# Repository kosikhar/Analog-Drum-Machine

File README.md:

# Analog-Drum-Machine
Capstone 2019 Analog Drum Machine project.

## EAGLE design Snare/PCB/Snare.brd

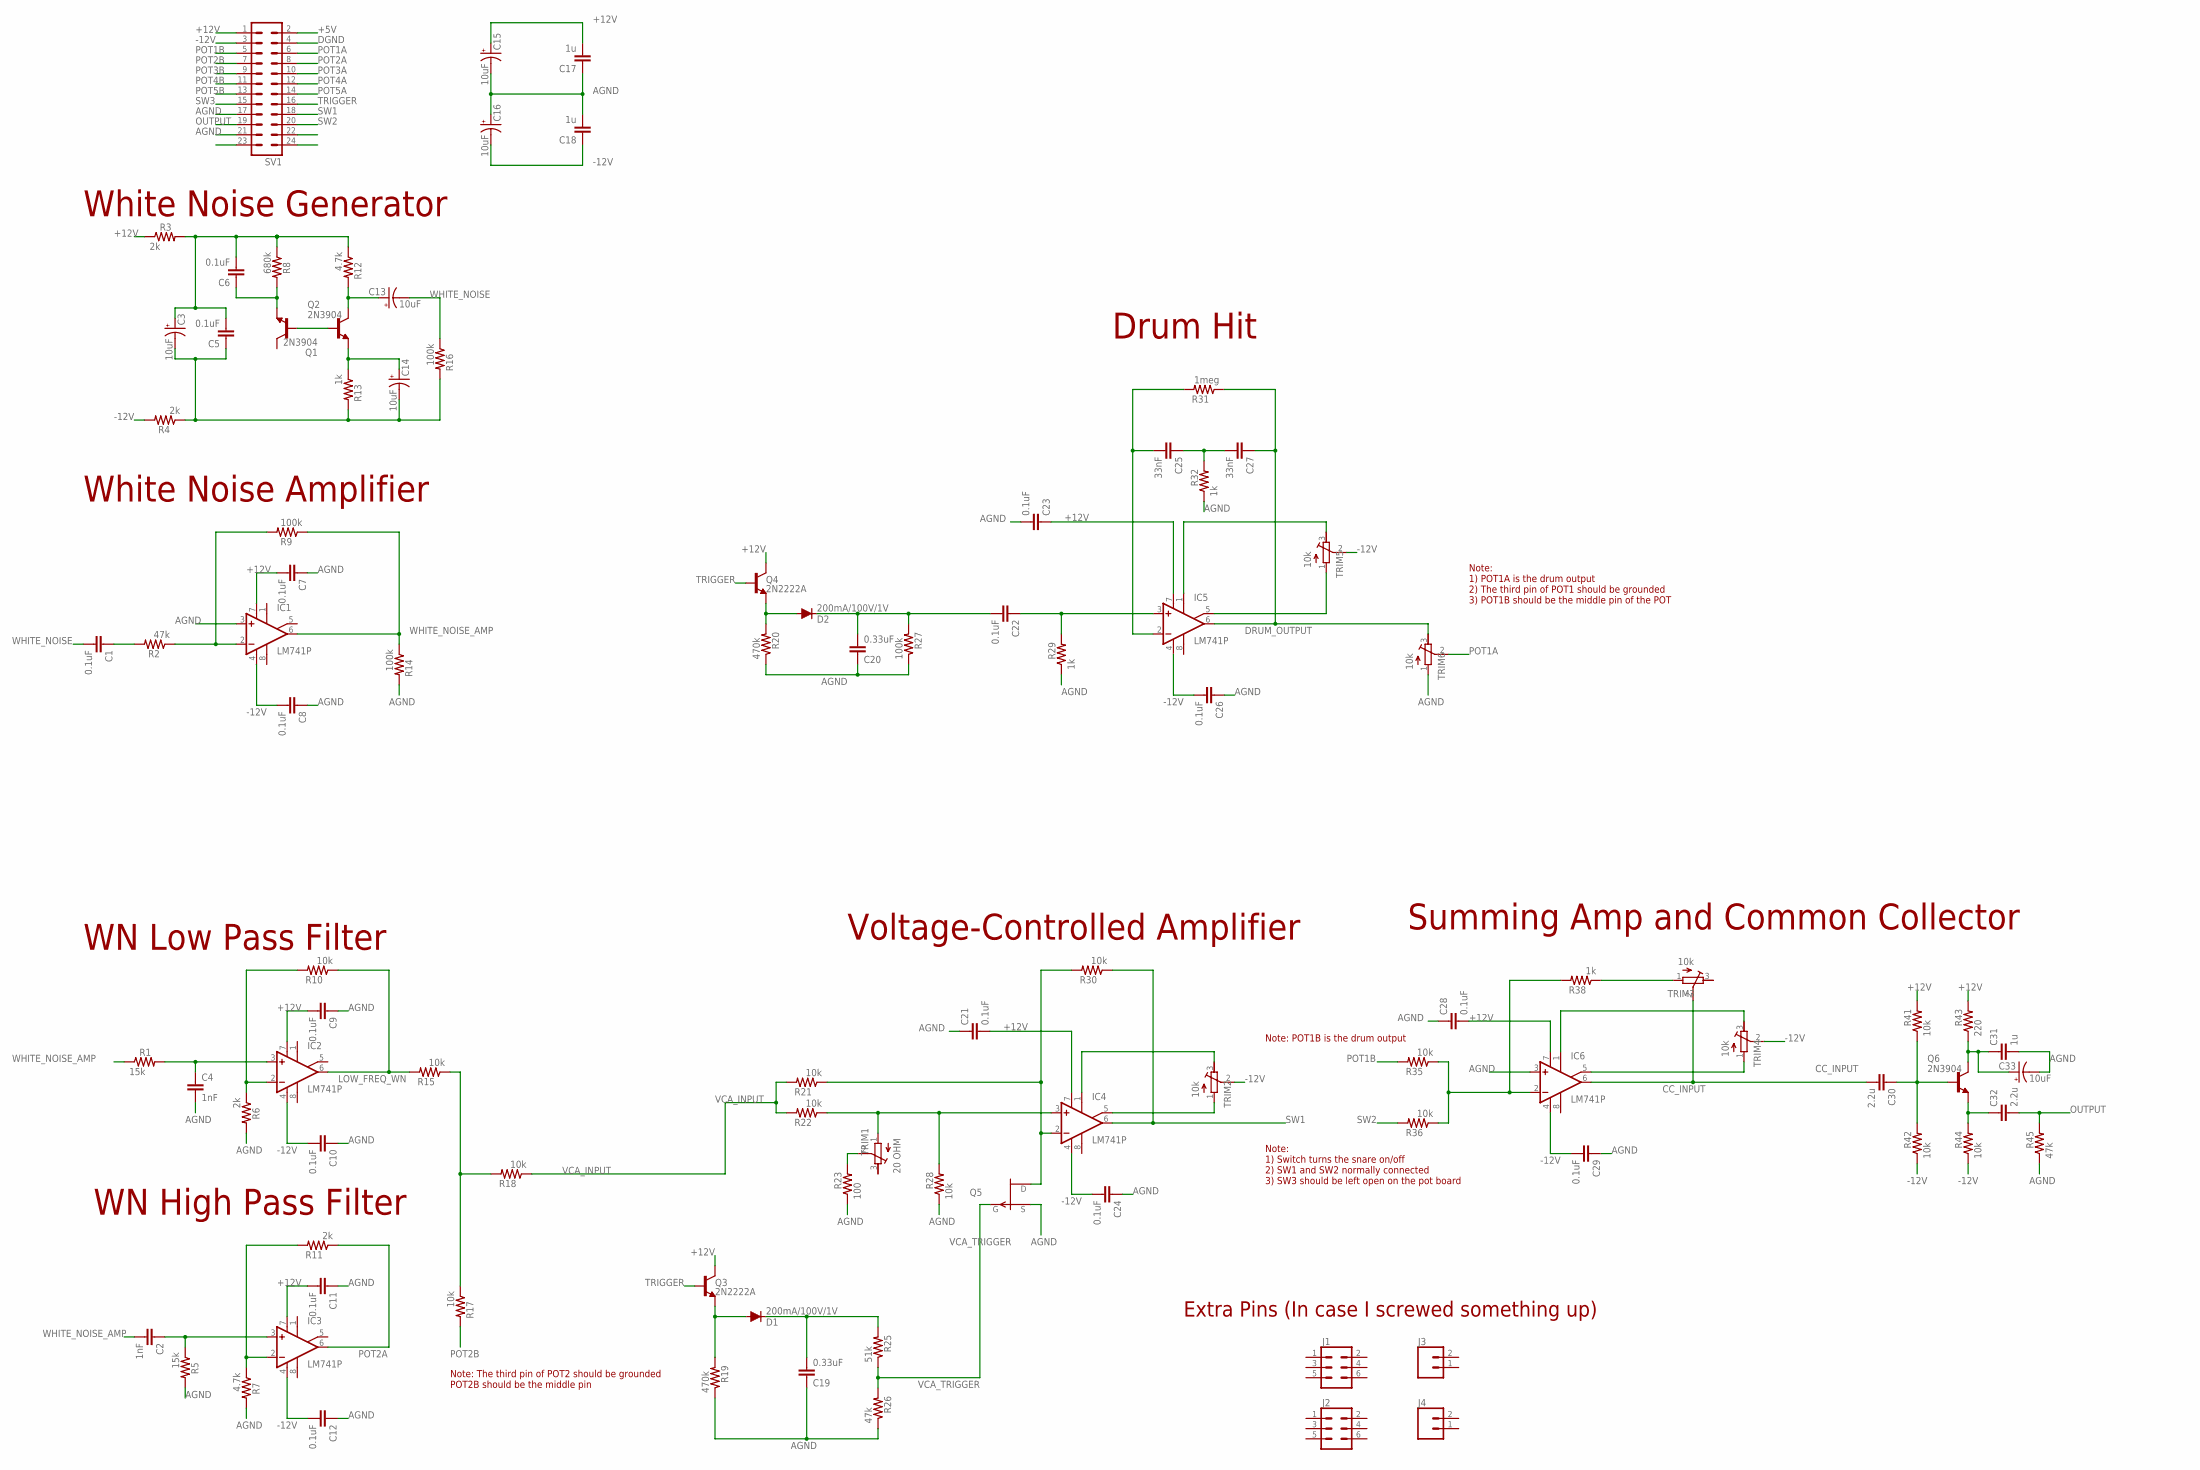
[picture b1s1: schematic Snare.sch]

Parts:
C1, C5, C6, C7, C8, C9, C10, C11, C12, C21, C22, C23, C24, C26, C28, C29: 0.1uF; C050-024X044
C2, C4: 1nF; C050-024X044
C3, C13, C14, C15, C16, C33: 10uF; E2,5-6
C17, C18, C31: 1u; C050-024X044
C19, C20: 0.33uF; C050-024X044
C25, C27: 33nF; C050-024X044
C30, C32: 2.2u; C050-024X044
D1, D2: 200mA/100V/1V; DIODE-1N4148
IC1, IC2, IC3, IC4, IC5, IC6: LM741P; DIL08
J1, J2: CONN_03X2NO_SILK; 2X3-NS
J3, J4: CONN_021X02_NO_SILK; 1X02_NO_SILK
Q1, Q2, Q6: 2N3904; TO92
Q3, Q4: 2N2222A; TO-92
Q5: J176; TO-92
R1, R5: 15k; 0207/10
R2, R26, R45: 47k; 0207/10
R3, R4, R6, R11: 2k; 0207/10
R7, R12: 4.7k; 0207/10
R8: 680k; 0207/10
R9, R14, R16, R27: 100k; 0207/10
R10, R15, R17, R18, R21, R22, R28, R30, R35, R36, R41, R42, R44: 10k; 0207/10
R13, R29, R32, R38: 1k; 0207/10
R19, R20: 470k; 0207/10
R23: 100; 0207/10
R25: 51k; 0207/10
R31: 1meg; 0207/10
R43: 220; 0207/10
SV1: MA12-2
TRIM1: 20 OHM; RTRIM64W
TRIM2, TRIM3, TRIM4, TRIM5, TRIM6: 10k; RTRIM64W

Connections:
+5V: SV1.2
+12V: C7.2, C9.2, C11.2, C15.+, C17.2, C21.2, C23.1, C28.2, IC1.7 (V+), IC2.7 (V+), IC3.7 (V+), IC4.7 (V+), IC5.7 (V+), IC6.7 (V+), Q3.1 (C), Q4.1 (C), R3.1, R41.2, R43.2, SV1.1
-12V: C8.2, C10.2, C12.2, C16.-, C18.1, C24.2, C26.2, C29.2, IC1.4 (V-), IC2.4 (V-), IC3.4 (V-), IC4.4 (V-), IC5.4 (V-), IC6.4 (V-), R4.2, R42.1, R44.1, SV1.3, TRIM2.2 (S), TRIM4.2 (S), TRIM5.2 (S)
AGND: C4.2, C7.1, C8.1, C9.1, C10.1, C11.1, C12.1, C15.-, C16.+, C17.1, C18.2, C19.1, C20.1, C21.1, C23.2, C24.1, C26.1, C28.1, C29.1, C31.2, C33.-, IC1.3 (+IN), IC6.3 (+IN), Q5.3 (S), R5.2, R6.2, R7.2, R14.2, R19.1, R20.1, R23.1, R26.1, R27.1, R28.1, R29.1, R32.1, R45.1, SV1.17, SV1.21, TRIM6.1 (A)
CC_INPUT: C30.2, IC6.6 (OUT), TRIM3.2 (S)
DGND: SV1.4
DRUM_OUTPUT: C27.1, IC5.6 (OUT), R31.1, TRIM6.3 (E)
unnamed: R15.1, R17.1, R18.2
unnamed: IC6.2 (-IN), R35.1, R36.1, R38.2
unnamed: R38.1, TRIM3.1 (A)
unnamed: IC6.5 (ON2), TRIM4.1 (A)
unnamed: C14.+, Q2.3 (E), R13.1
unnamed: C3.+, C5.2, C6.2, R3.2, R8.1, R12.1
unnamed: IC6.1 (ON1), TRIM4.3 (E)
unnamed: C25.1, C27.2, R32.2
unnamed: Q1.2 (B), Q2.2 (B)
unnamed: C6.1, Q1.3 (E), R8.2
unnamed: C3.-, C5.1, C14.-, R4.1, R13.2, R16.2
unnamed: IC1.2 (-IN), R2.1, R9.2
unnamed: IC3.2 (-IN), R7.1, R11.2
unnamed: C1.1, R2.2
unnamed: C13.+, Q2.1 (C), R12.2
unnamed: C2.1, IC3.3 (+IN), R5.1
unnamed: IC2.2 (-IN), R6.1, R10.2
unnamed: C4.1, IC2.3 (+IN), R1.2
unnamed: C20.2, C22.2, D2.C, R27.2
unnamed: C30.1, Q6.2 (B), R41.1, R42.2
unnamed: C32.1, Q6.3 (E), R44.2
unnamed: C31.1, C33.+, Q6.1 (C), R43.1
unnamed: D2.A, Q4.3 (E), R20.2
unnamed: C22.1, IC5.3 (+IN), R29.2
unnamed: R23.2, TRIM1.2 (S)
unnamed: C25.2, IC5.2 (-IN), R31.2
unnamed: IC5.1 (ON1), TRIM5.3 (E)
unnamed: IC5.5 (ON2), TRIM5.1 (A)
unnamed: IC4.3 (+IN), R22.1, R28.2, TRIM1.1 (A)
unnamed: IC4.2 (-IN), Q5.1 (D), R21.1, R30.2
unnamed: IC4.1 (ON1), TRIM2.3 (E)
unnamed: C19.2, D1.C, R25.2
unnamed: IC4.5 (ON2), TRIM2.1 (A)
unnamed: D1.A, Q3.3 (E), R19.2
OUTPUT: C32.2, R45.2, SV1.19
POT1A: SV1.6, TRIM6.2 (S)
POT1B: R35.2, SV1.5
POT2B: R17.2, SV1.7
POT3A: SV1.10
POT3B: SV1.9
POT4A: SV1.12
POT4B: SV1.11
POT5A: SV1.14
POT5B: SV1.13
SW1: IC4.6 (OUT), R30.1, SV1.18
SW2: R36.2, SV1.20
SW3: SV1.15
TRIGGER: Q3.2 (B), Q4.2 (B), SV1.16
VCA_INPUT: R18.1, R21.2, R22.2
VCA_TRIGGER: Q5.2 (G), R25.1, R26.2
WHITE_NOISE: C1.2, C13.-, R16.1

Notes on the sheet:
Note: The third pin of POT2 should be grounded POT2B should be the middle pin
Note: 1) POT1A is the drum output 2) The third pin of POT1 should be grounded 3) POT1B should be the middle pin of the POT
Note: POT1B is the drum output
Note: 1) Switch turns the snare on/off 2) SW1 and SW2 normally connected 3) SW3 should be left open on the pot board
White Noise Generator
White Noise Amplifier
WN Low Pass Filter
WN High Pass Filter
Drum Hit
Voltage-Controlled Amplifier
Summing Amp and Common Collector
Extra Pins (In case I screwed something up)

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
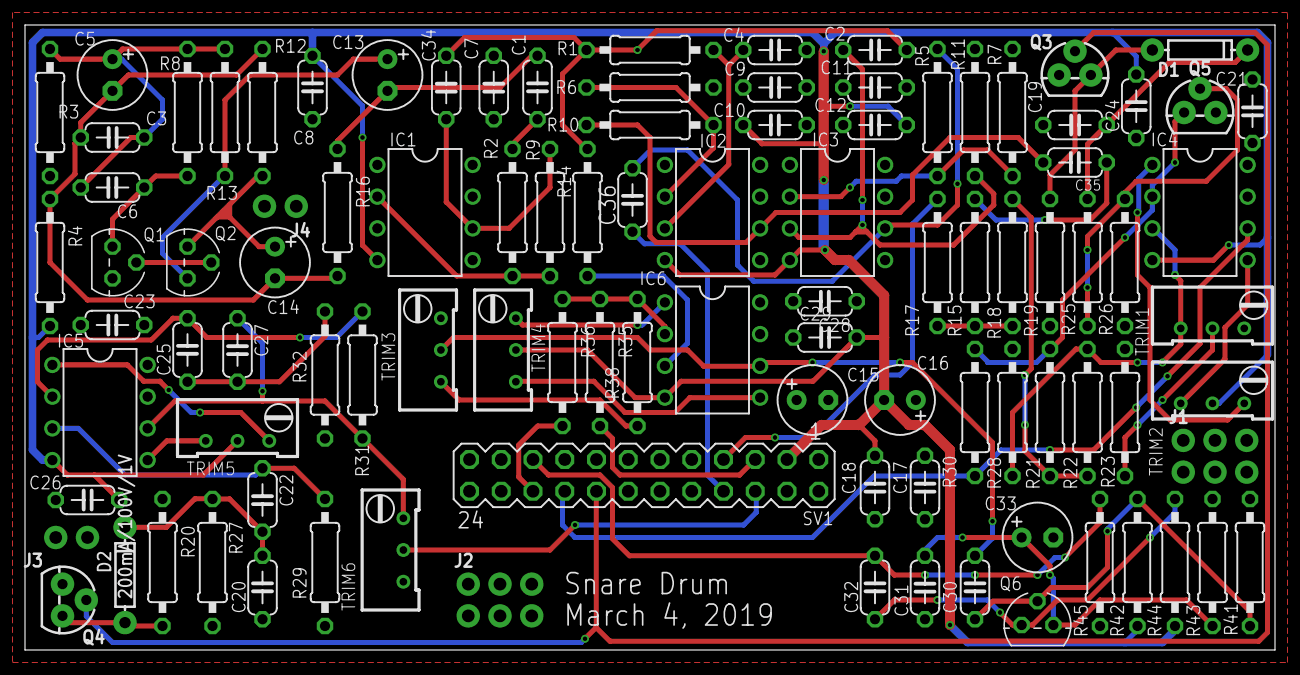
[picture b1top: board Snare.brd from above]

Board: 2 copper layers, 100.0 x 50.0 mm, 100 parts (0 on the bottom side), 55 nets.

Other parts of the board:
C34, C35, C36: 0.1uF; C050-024X044

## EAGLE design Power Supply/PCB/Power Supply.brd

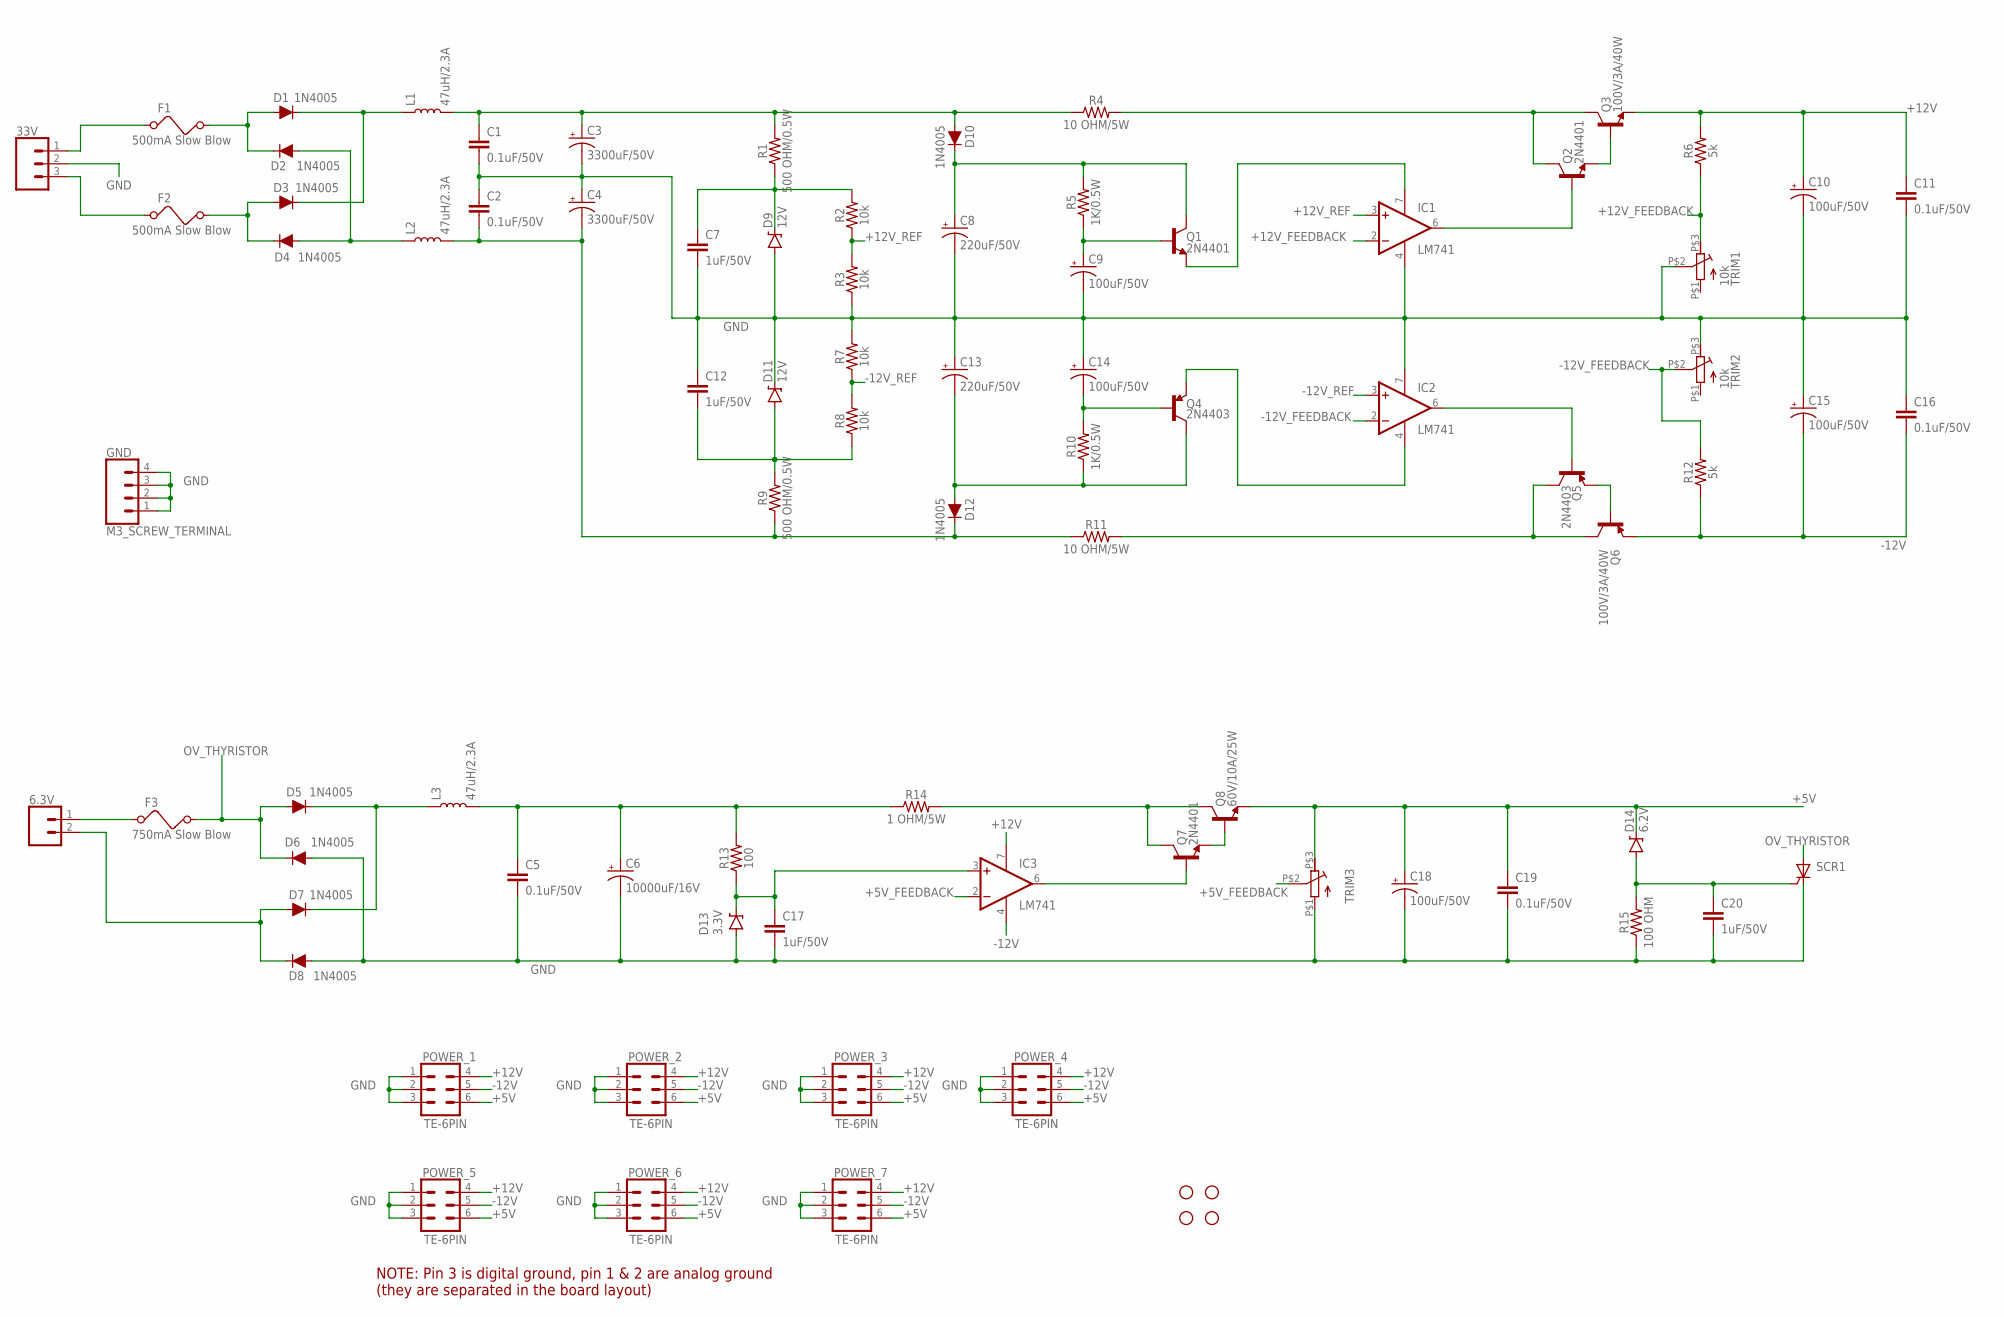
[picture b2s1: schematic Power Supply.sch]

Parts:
6.3V: TE-2PIN; 2_PIN_CONNECT
33V: TE-3PIN; 3_PIN_TE
C1, C2, C5, C11, C16, C19: 0.1uF/50V; CERAMIC_CAPACITOR
C3, C4: 3300uF/50V; POLARIZED_CAP_3300UF
C6: 10000uF/16V; POLARIZED_CAP_3300UF
C7, C12, C17, C20: 1uF/50V; CERAMIC_CAPACITOR
C8, C13: 220uF/50V; 220UF_CAP
C9, C10, C14, C15, C18: 100uF/50V; 100UF_CAP
D1, D2, D3, D4, D5, D6, D7, D8, D10, D12: 1N4005; DIODE-1N4001
D9, D11: 12V; 1W_ZENER
D13: 3.3V; 1W_ZENER
D14: 6.2V; 1W_ZENER
F1, F2: 500mA Slow Blow; FUSEHOLDER
F3: 750mA Slow Blow; FUSEHOLDER
GND: M3_SCREW_TERMINAL
H1, H2, H3, H4: STAND-OFF
IC1, IC2, IC3: LM741; DIL08
L1, L2, L3: 47uH/2.3A; 47UH_2.3A_COIL
POWER_1, POWER_2, POWER_3, POWER_4, POWER_5, POWER_6, POWER_7: TE-6PIN; TE_6_PIN
Q1, Q2, Q7: 2N4401; TO-92
Q3, Q6: 100V/3A/40W; TO-220_LARGE_HEATSINK
Q4, Q5: 2N4403; TO-92
Q8: 60V/10A/25W; TO-220_SMALL_HEATSINK
R1, R9: 500 OHM/0.5W; 0.5W_RES
R2, R3, R7, R8: 10k; 0.25W_RES
R4, R11: 10 OHM/5W; 5W_RES
R5, R10: 1K/0.5W; 0.5W_RES
R6, R12: 5k; 0.25W_RES
R13: 100; 0.25W_RES
R14: 1 OHM/5W; 5W_RES
R15: 100 OHM; 0.25W_RES
SCR1: THYRISTOR_4A; TO220V
TRIM1, TRIM2: 10k; 10K_TRIM
TRIM3: 10K_TRIMMER; 10K_TRIM

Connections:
+5V: C18.P1+ (+), C19.P$1 (1), D14.P$2CATHODE (C), POWER_1.6, POWER_2.6, POWER_3.6, POWER_4.6, POWER_5.6, POWER_6.6, POWER_7.6, Q8.P$3 (E), TRIM3.P$3 (E)
+5V_FEEDBACK: IC3.2 (-IN), TRIM3.P$2 (S)
+12V: C10.P1+ (+), C11.P$1 (1), IC3.7 (V+), POWER_1.4 (2), POWER_2.4 (2), POWER_3.4 (2), POWER_4.4 (2), POWER_5.4 (2), POWER_6.4 (2), POWER_7.4 (2), Q3.P$3 (E), R6.P$2 (2)
+12V_FEEDBACK: IC1.2 (-IN), R6.P$1 (1), TRIM1.P$3 (E)
+12V_REF: IC1.3 (+IN), R2.P$1 (1), R3.P$2 (2)
-12V: C15.P2- (-), C16.P$2 (2), IC3.4 (V-), POWER_1.5 (4), POWER_2.5 (4), POWER_3.5 (4), POWER_4.5 (4), POWER_5.5 (4), POWER_6.5 (4), POWER_7.5 (4), Q6.P$3 (E), R12.P$1 (1)
-12V_FEEDBACK: IC2.2 (-IN), R12.P$2 (2), TRIM2.P$2 (S)
-12V_REF: IC2.3 (+IN), R7.P$1 (1), R8.P$2 (2)
GND: 33V.2, C1.P$2 (2), C2.P$1 (1), C3.P2- (-), C4.P1+ (+), C5.P$2 (2), C6.P2- (-), C7.P$2 (2), C8.P2- (-), C9.P2- (-), C10.P2- (-), C11.P$2 (2), C12.P$1 (1), C13.P1+ (+), C14.P1+ (+), C15.P1+ (+), C16.P$1 (1), C17.P$2 (2), C18.P2- (-), C19.P$2 (2), C20.P$2 (2), D6.A, D8.A, D9.P$1ANODE (A), D11.P$2CATHODE (C), D13.P$1ANODE (A), GND.1, GND.2, GND.3, GND.4, IC1.4 (V-), IC2.7 (V+), POWER_1.1, POWER_1.2 (3), POWER_1.3 (5), POWER_2.1, POWER_2.2 (3), POWER_2.3 (5), POWER_3.1, POWER_3.2 (3), POWER_3.3 (5), POWER_4.1, POWER_4.2 (3), POWER_4.3 (5), POWER_5.1, POWER_5.2 (3), POWER_5.3 (5), POWER_6.1, POWER_6.2 (3), POWER_6.3 (5), POWER_7.1, POWER_7.2 (3), POWER_7.3 (5), R3.P$1 (1), R7.P$2 (2), R15.P$1 (1), SCR1.1 (C), TRIM1.P$2 (S), TRIM2.P$3 (E), TRIM3.P$1 (A)
unnamed: D1.C, D3.C, L1.P$1 (1)
unnamed: D1.A, D2.C, F1.P$2 (2)
unnamed: D3.A, D4.C, F2.P$2 (2)
unnamed: D2.A, D4.A, L2.P$1 (1)
unnamed: 33V.1 (3), F1.P$1 (1)
unnamed: 33V.3 (1), F2.P$1 (1)
unnamed: C1.P$1 (1), C3.P1+ (+), D10.A, L1.P$2 (2), R1.P$2 (2), R4.P$1 (1)
unnamed: C8.P1+ (+), D10.C, Q1.3 (C), R5.P$2 (2)
unnamed: C2.P$2 (2), C4.P2- (-), D12.C, L2.P$2 (2), R9.P$1 (1), R11.P$1 (1)
unnamed: C9.P1+ (+), Q1.2 (B), R5.P$1 (1)
unnamed: IC1.7 (V+), Q1.1 (E)
unnamed: Q2.3 (C), Q3.P$2 (C), R4.P$2 (2)
unnamed: Q2.1 (E), Q3.P$1 (B)
unnamed: IC1.6 (OUT), Q2.2 (B)
unnamed: C7.P$1 (1), D9.P$2CATHODE (C), R1.P$1 (1), R2.P$2 (2)
unnamed: C13.P2- (-), D12.A, Q4.3 (C), R10.P$1 (1)
unnamed: C17.P$1 (1), D13.P$2CATHODE (C), IC3.3 (+IN), R13.P$1 (1)
unnamed: C12.P$2 (2), D11.P$1ANODE (A), R8.P$1 (1), R9.P$2 (2)
unnamed: 6.3V.1 (2), F3.P$1 (1)
unnamed: C14.P2- (-), Q4.2 (B), R10.P$2 (2)
unnamed: IC2.4 (V-), Q4.1 (E)
unnamed: Q5.3 (C), Q6.P$2 (C), R11.P$2 (2)
unnamed: Q5.1 (E), Q6.P$1 (B)
unnamed: IC2.6 (OUT), Q5.2 (B)
unnamed: Q7.3 (C), Q8.P$2 (C), R14.P$2 (2)
unnamed: 6.3V.2 (1), D7.A, D8.C
unnamed: IC3.6 (OUT), Q7.2 (B)
unnamed: D5.C, D7.C, L3.P$1 (1)
unnamed: C5.P$1 (1), C6.P1+ (+), L3.P$2 (2), R13.P$2 (2), R14.P$1 (1)
unnamed: Q7.1 (E), Q8.P$1 (B)
unnamed: C20.P$1 (1), D14.P$1ANODE (A), R15.P$2 (2), SCR1.3 (G)
OV_THYRISTOR: D5.A, D6.C, F3.P$2 (2), SCR1.2 (A)

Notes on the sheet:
NOTE: Pin 3 is digital ground, pin 1 & 2 are analog ground (they are separated in the board layout)

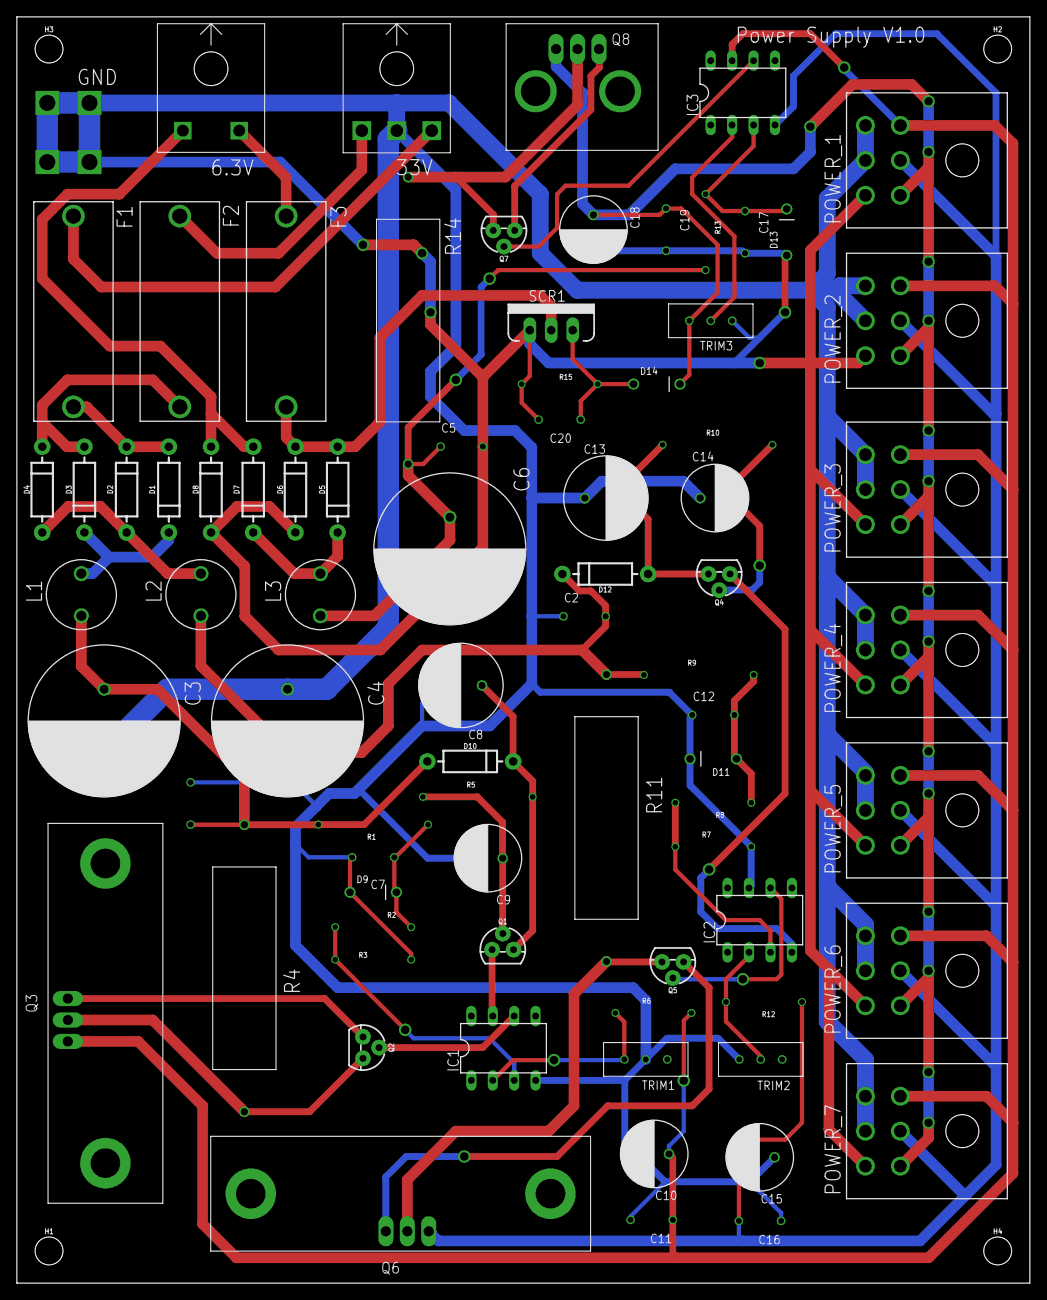
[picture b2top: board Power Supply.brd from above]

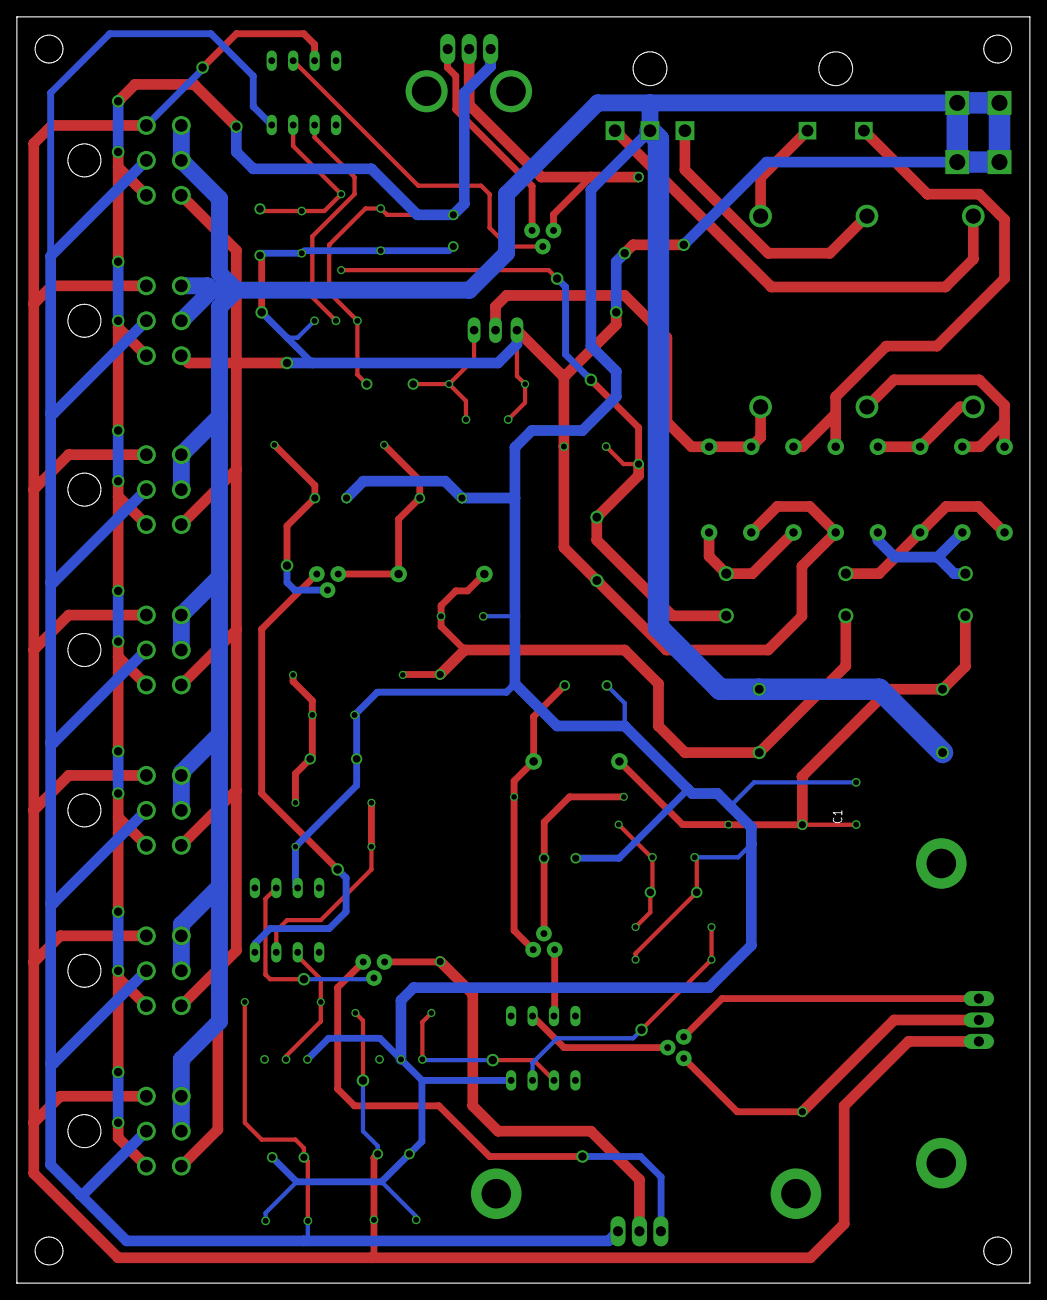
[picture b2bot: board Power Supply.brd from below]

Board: 2 copper layers, 120.0 x 150.0 mm, 84 parts (2 on the bottom side), 41 nets.

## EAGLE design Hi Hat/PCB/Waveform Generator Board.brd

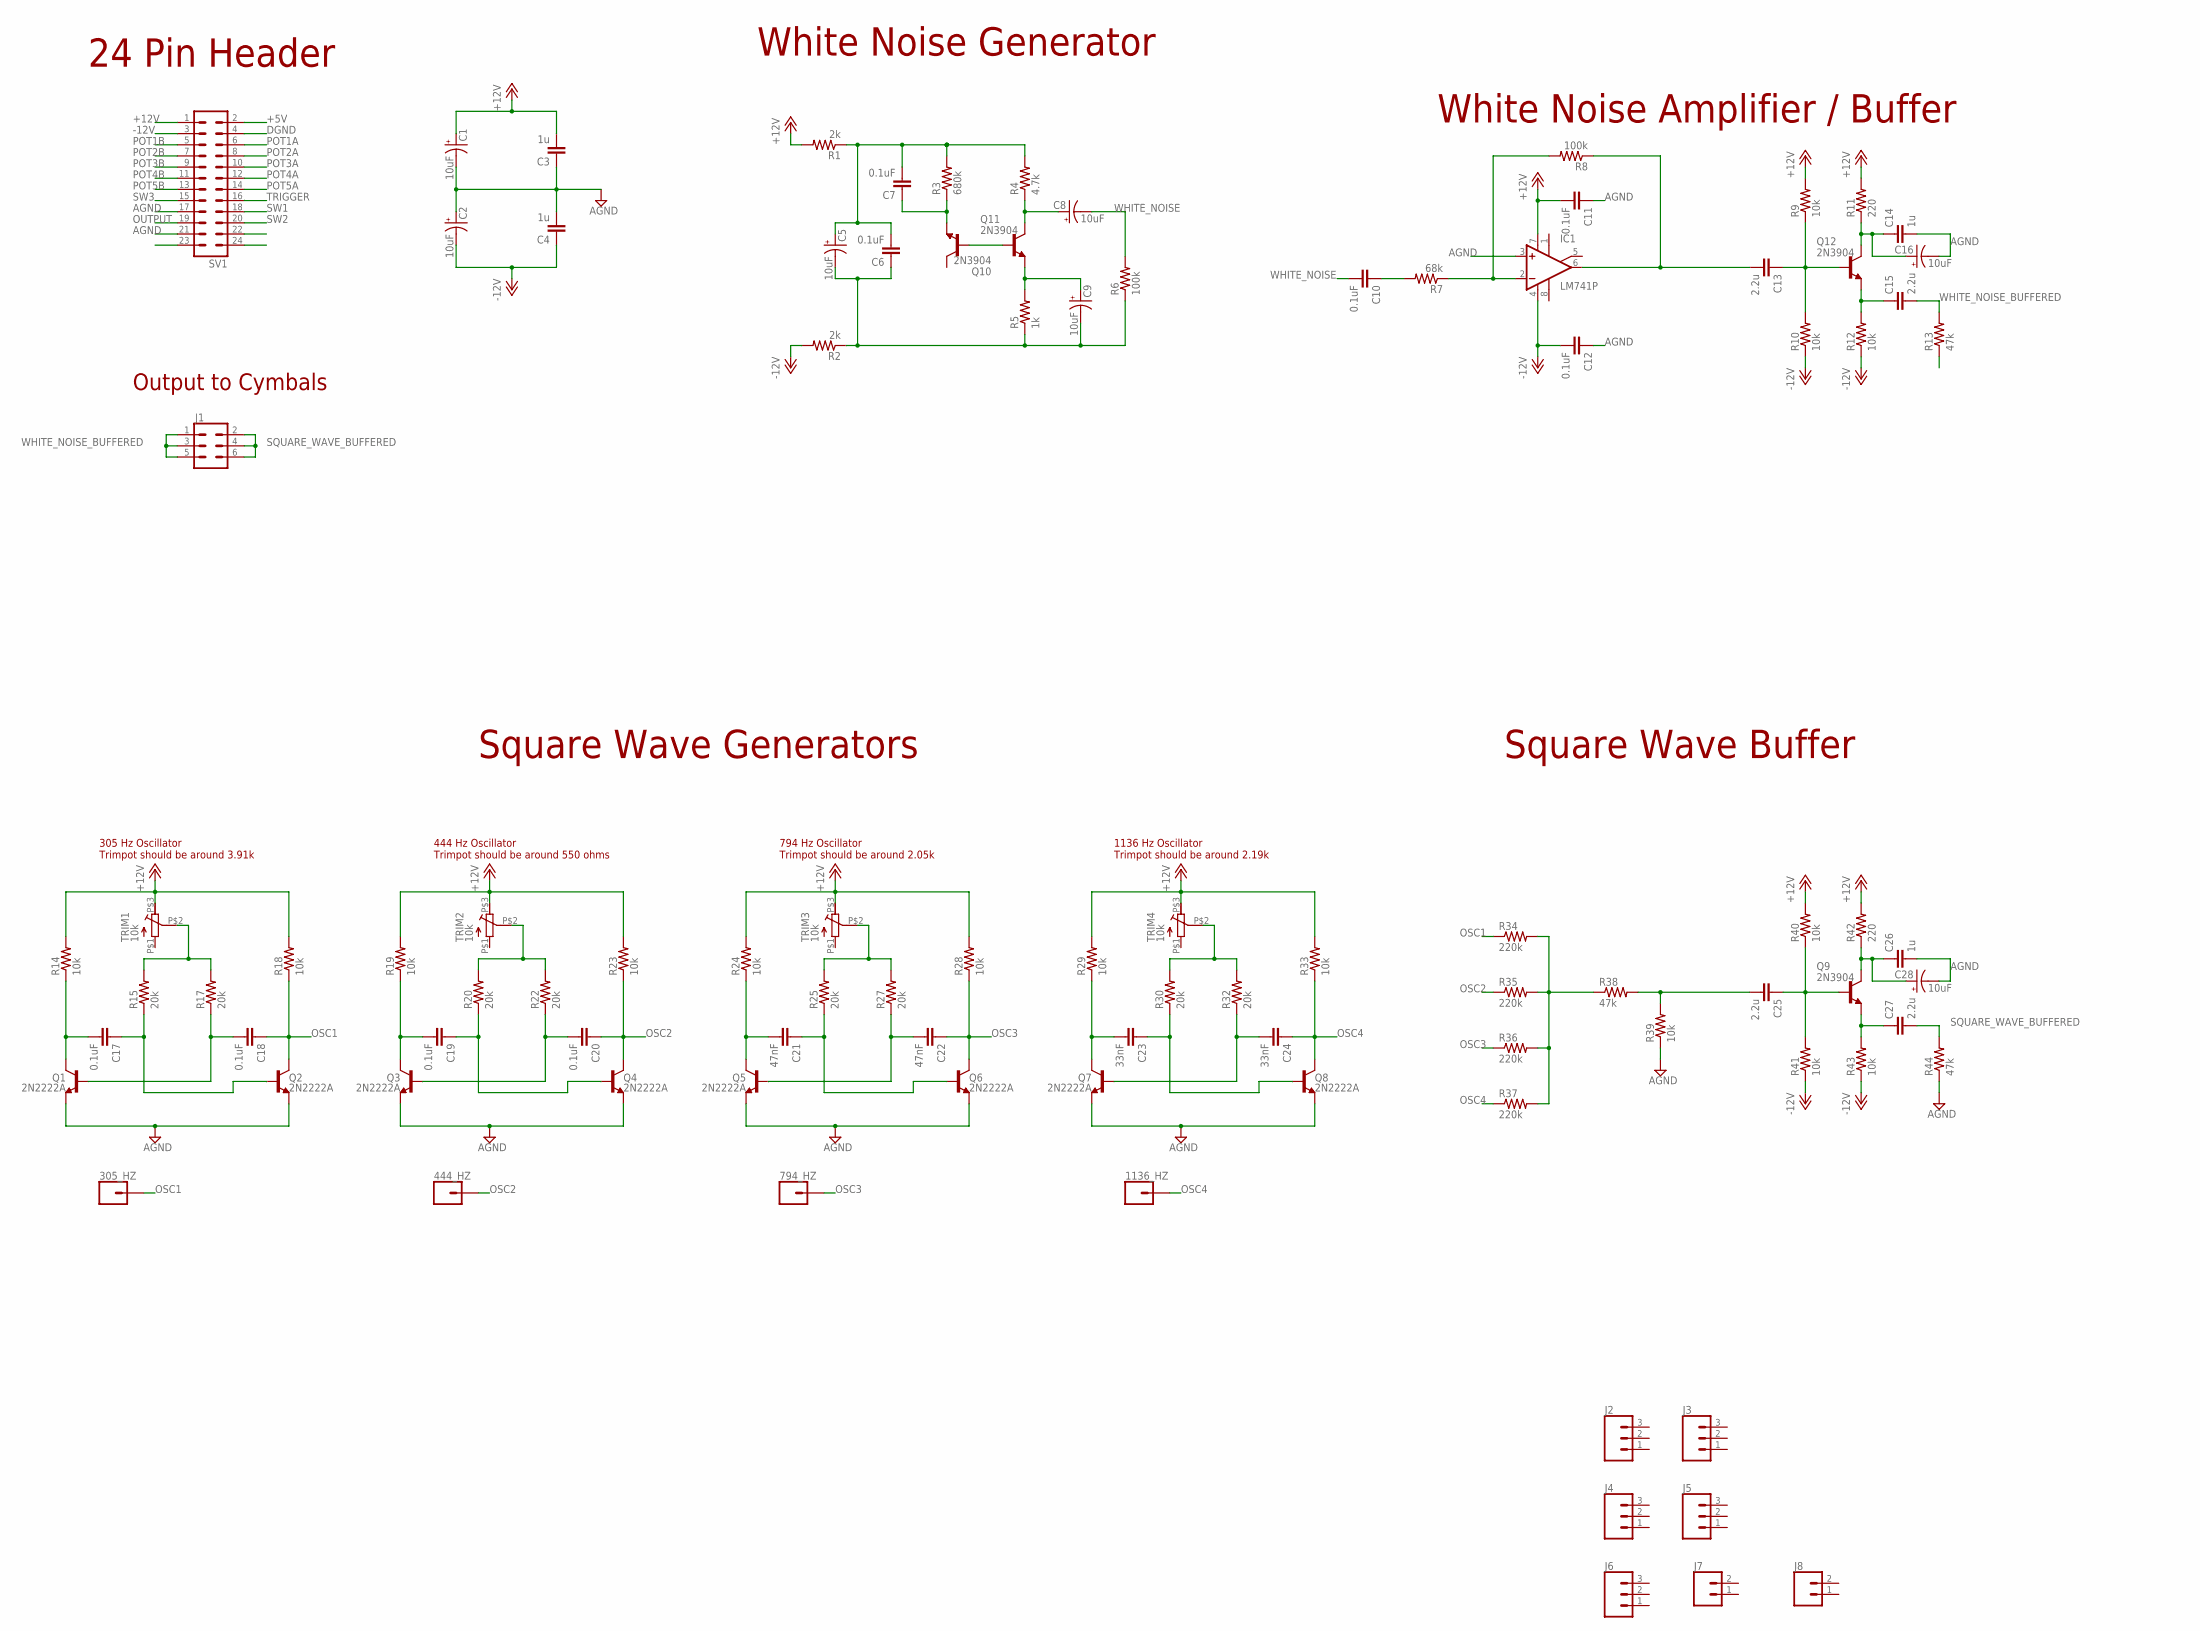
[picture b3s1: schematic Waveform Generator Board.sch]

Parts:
305_HZ, 444_HZ, 794_HZ, 1136_HZ: CONN_01PTH_NO_SILK_KIT; 1X01NS_KIT
C1, C2, C5, C8, C9, C16, C28: 10uF; E2,5-6
C3, C4, C14, C26: 1u; C050-024X044
C6, C7, C10, C11, C12, C17, C18, C19, C20: 0.1uF; C050-024X044
C13, C15, C25, C27: 2.2u; C050-024X044
C21, C22: 47nF; C050-024X044
C23, C24: 33nF; C050-024X044
IC1: LM741P; DIL08
J1: CONN_03X2NO_SILK; 2X3-NS
J2, J3, J4, J5, J6: CONN_031X03_NO_SILK; 1X03_NO_SILK
J7, J8: CONN_021X02_NO_SILK; 1X02_NO_SILK
Q1, Q2, Q3, Q4, Q5, Q6, Q7, Q8: 2N2222A; TO-92
Q9, Q10, Q11, Q12: 2N3904; TO92
R1, R2: 2k; 0207/7
R3: 680k; 0207/7
R4: 4.7k; 0207/7
R5: 1k; 0207/7
R6, R8: 100k; 0207/7
R7: 68k; 0207/7
R9, R10, R12, R14, R18, R19, R23, R24, R28, R29, R33, R39, R40, R41, R43: 10k; 0207/7
R11, R42: 220; 0207/7
R13, R38, R44: 47k; 0207/7
R15, R17, R20, R22, R25, R27, R30, R32: 20k; 0207/7
R34, R35, R36, R37: 220k; 0207/7
SV1: MA12-2
TRIM1, TRIM2, TRIM3, TRIM4: 10k; 10K_TRIM

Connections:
+5V: SV1.2
+12V: C1.+, C3.2, C11.2, IC1.7 (V+), R1.2, R9.2, R11.2, R14.2, R18.2, R19.2, R23.2, R24.2, R28.2, R29.2, R33.2, R40.2, R42.2, SV1.1, TRIM1.P$3 (E), TRIM2.P$3 (E), TRIM3.P$3 (E), TRIM4.P$3 (E)
-12V: C2.-, C4.1, C12.2, IC1.4 (V-), R2.2, R10.1, R12.1, R41.1, R43.1, SV1.3
AGND: C1.-, C2.+, C3.1, C4.2, C11.1, C12.1, C14.2, C16.-, C26.2, C28.-, IC1.3 (+IN), Q1.3 (E), Q2.3 (E), Q3.3 (E), Q4.3 (E), Q5.3 (E), Q6.3 (E), Q7.3 (E), Q8.3 (E), R13.1, R39.1, R44.1, SV1.17, SV1.21
DGND: SV1.4
unnamed: C13.1, Q12.2 (B), R9.1, R10.2
unnamed: C15.1, Q12.3 (E), R12.2
unnamed: C14.1, C16.+, Q12.1 (C), R11.1
unnamed: C9.+, Q11.3 (E), R5.2
unnamed: C5.+, C6.2, C7.2, R1.1, R3.2, R4.2
unnamed: C13.2, IC1.6 (OUT), R8.1
unnamed: C17.2, Q1.1 (C), R14.1
unnamed: C17.1, Q2.2 (B), R15.1
unnamed: C18.2, Q1.2 (B), R17.1
unnamed: R15.2, R17.2, TRIM1.P$2 (S)
unnamed: C19.2, Q3.1 (C), R19.1
unnamed: Q10.2 (B), Q11.2 (B)
unnamed: C19.1, Q4.2 (B), R20.1
unnamed: C20.2, Q3.2 (B), R22.1
unnamed: C7.1, Q10.3 (E), R3.1
unnamed: C5.-, C6.1, C9.-, R2.1, R5.1, R6.1
unnamed: R34.2, R35.2, R36.2, R37.2, R38.1
unnamed: IC1.2 (-IN), R7.1, R8.2
unnamed: C10.1, R7.2
unnamed: R20.2, R22.2, TRIM2.P$2 (S)
unnamed: C8.+, Q11.1 (C), R4.1
unnamed: C21.2, Q5.1 (C), R24.1
unnamed: C21.1, Q6.2 (B), R25.1
unnamed: C22.2, Q5.2 (B), R27.1
unnamed: R25.2, R27.2, TRIM3.P$2 (S)
unnamed: C23.2, Q7.1 (C), R29.1
unnamed: C23.1, Q8.2 (B), R30.1
unnamed: C24.2, Q7.2 (B), R32.1
unnamed: C25.2, R38.2, R39.2
unnamed: R30.2, R32.2, TRIM4.P$2 (S)
unnamed: C25.1, Q9.2 (B), R40.1, R41.2
unnamed: C27.1, Q9.3 (E), R43.2
unnamed: C26.1, C28.+, Q9.1 (C), R42.1
OSC1: 305_HZ.1, C18.1, Q2.1 (C), R18.1, R34.1
OSC2: 444_HZ.1, C20.1, Q4.1 (C), R23.1, R35.1
OSC3: 794_HZ.1, C22.1, Q6.1 (C), R28.1, R36.1
OSC4: 1136_HZ.1, C24.1, Q8.1 (C), R33.1, R37.1
OUTPUT: SV1.19
POT1A: SV1.6
POT1B: SV1.5
POT2A: SV1.8
POT2B: SV1.7
POT3A: SV1.10
POT3B: SV1.9
POT4A: SV1.12
POT4B: SV1.11
POT5A: SV1.14
POT5B: SV1.13
SQUARE_WAVE_BUFFERED: C27.2, J1.2, J1.4, J1.6, R44.2
SW1: SV1.18
SW2: SV1.20
SW3: SV1.15
TRIGGER: SV1.16
WHITE_NOISE: C8.-, C10.2, R6.2
WHITE_NOISE_BUFFERED: C15.2, J1.1, J1.3, J1.5, R13.2

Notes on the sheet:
White Noise Generator
White Noise Amplifier / Buffer
305 Hz Oscillator Trimpot should be around 3.91k
444 Hz Oscillator Trimpot should be around 550 ohms
794 Hz Oscillator Trimpot should be around 2.05k
1136 Hz Oscillator Trimpot should be around 2.19k
24 Pin Header
Output to Cymbals
Square Wave Generators
Square Wave Buffer

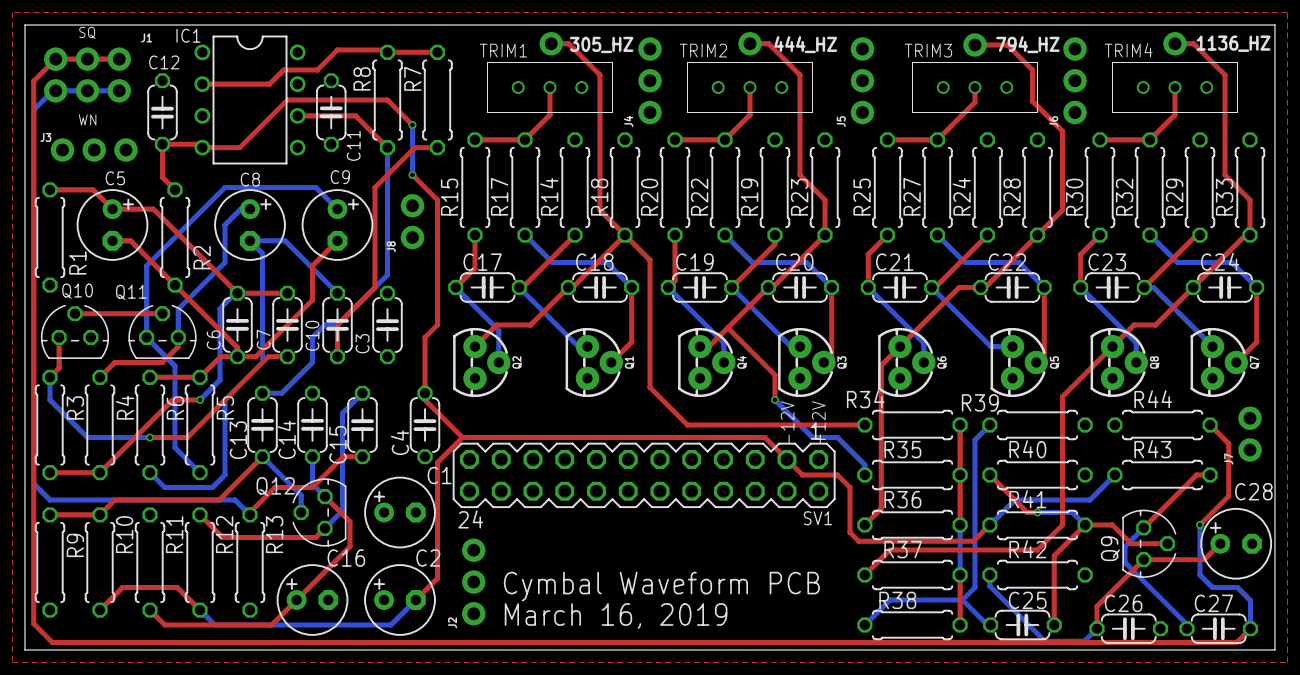
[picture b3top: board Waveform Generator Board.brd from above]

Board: 2 copper layers, 100.0 x 50.0 mm, 98 parts (0 on the bottom side), 43 nets.

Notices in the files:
parts and their libraries:
SparkFun-DiscreteSemi: Licensing: Creative Commons ShareAlike 4.0 International - https://creativecommons.org/licenses/by-sa/4.0
